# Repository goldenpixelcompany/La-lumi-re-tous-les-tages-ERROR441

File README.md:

# La lumière à tous les étages : ERROR 441
*Manuel pour allumer la lumière à tous les étages*

Voici un manuel pour apprendre à allumer la lumière à tous les étages. Et ce n’est pas toujours évident. Surtout lorsque les étages sont longs et grands et que la nature nous attribue une petite taille. Je fais un mètre soixante-neuf et j’avais besoin d’aide. Pour accomplir ma mission, je dû me faire une amie. Mais cette amie n’existait pas et nous l’avons inventée avec d’autres amis.

**Partie I : dispositif**

Nous avons choisi de réaliser cette experience à lécole des arts décoratifs de Paris. Nous étions nombreux à vouloir accomplir cette mission. Voici le batiment concerné avant et après la lumière allumée : 

Composée de 441 fenêtres d’un mètre sur un mètre vingt, la baie vitrée de l'école s’étale sur 25 mètres de haut et 21 mètres de large. Chaque fenêtre se transformerait en pixel à l'aide d'un dispositif numérique composé de Leds RGB et de papier. Tous ces dispositifs sont connectés ensembles et forment un écran dit micro-géant : Immense par ses dimensions et minuscule par sa résolution.

**Partie II : Hardware**

Pour connecter ces oixels entre eux, nous avons développer un circuit électronique adapté. Chacun d'entre eux controllait 3 pixels. Nous appelions donc les circuits les *métapixels*. Il y avait 147 circuits tous connectés en WIFI et commander par la puce ESP32. Le voici : 

**Partie III : Software**

Pour controller cet écran de pixels géant nous avons developpé le software *SEND PIX*. Essentiellement developpé par Lorris Sahli, le logiciel est à la croisée d'un outil de dessin, de gestion de pixels et d'un instrument de VJing en direct. 

Résultat des animations dessinées par le logiciel SEND PIX :

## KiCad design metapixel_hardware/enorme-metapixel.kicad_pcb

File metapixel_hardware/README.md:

# metapixel

PCB made for control the pixels on the facade. By three they come.

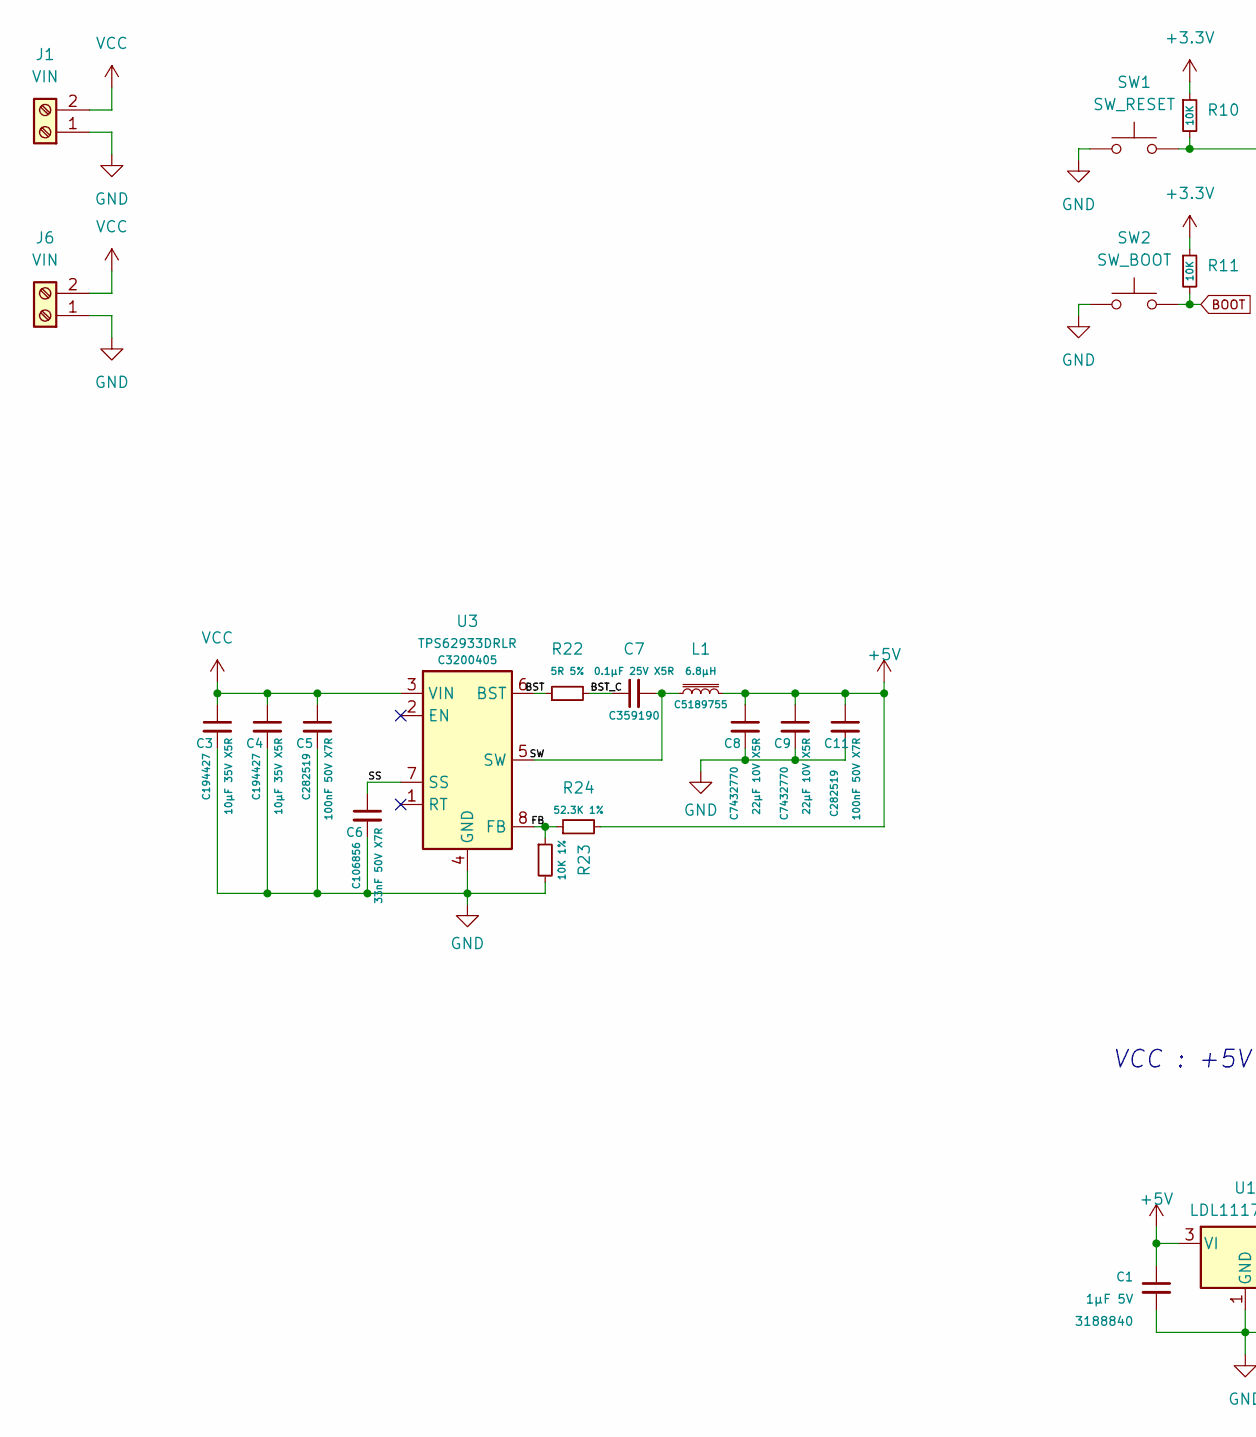
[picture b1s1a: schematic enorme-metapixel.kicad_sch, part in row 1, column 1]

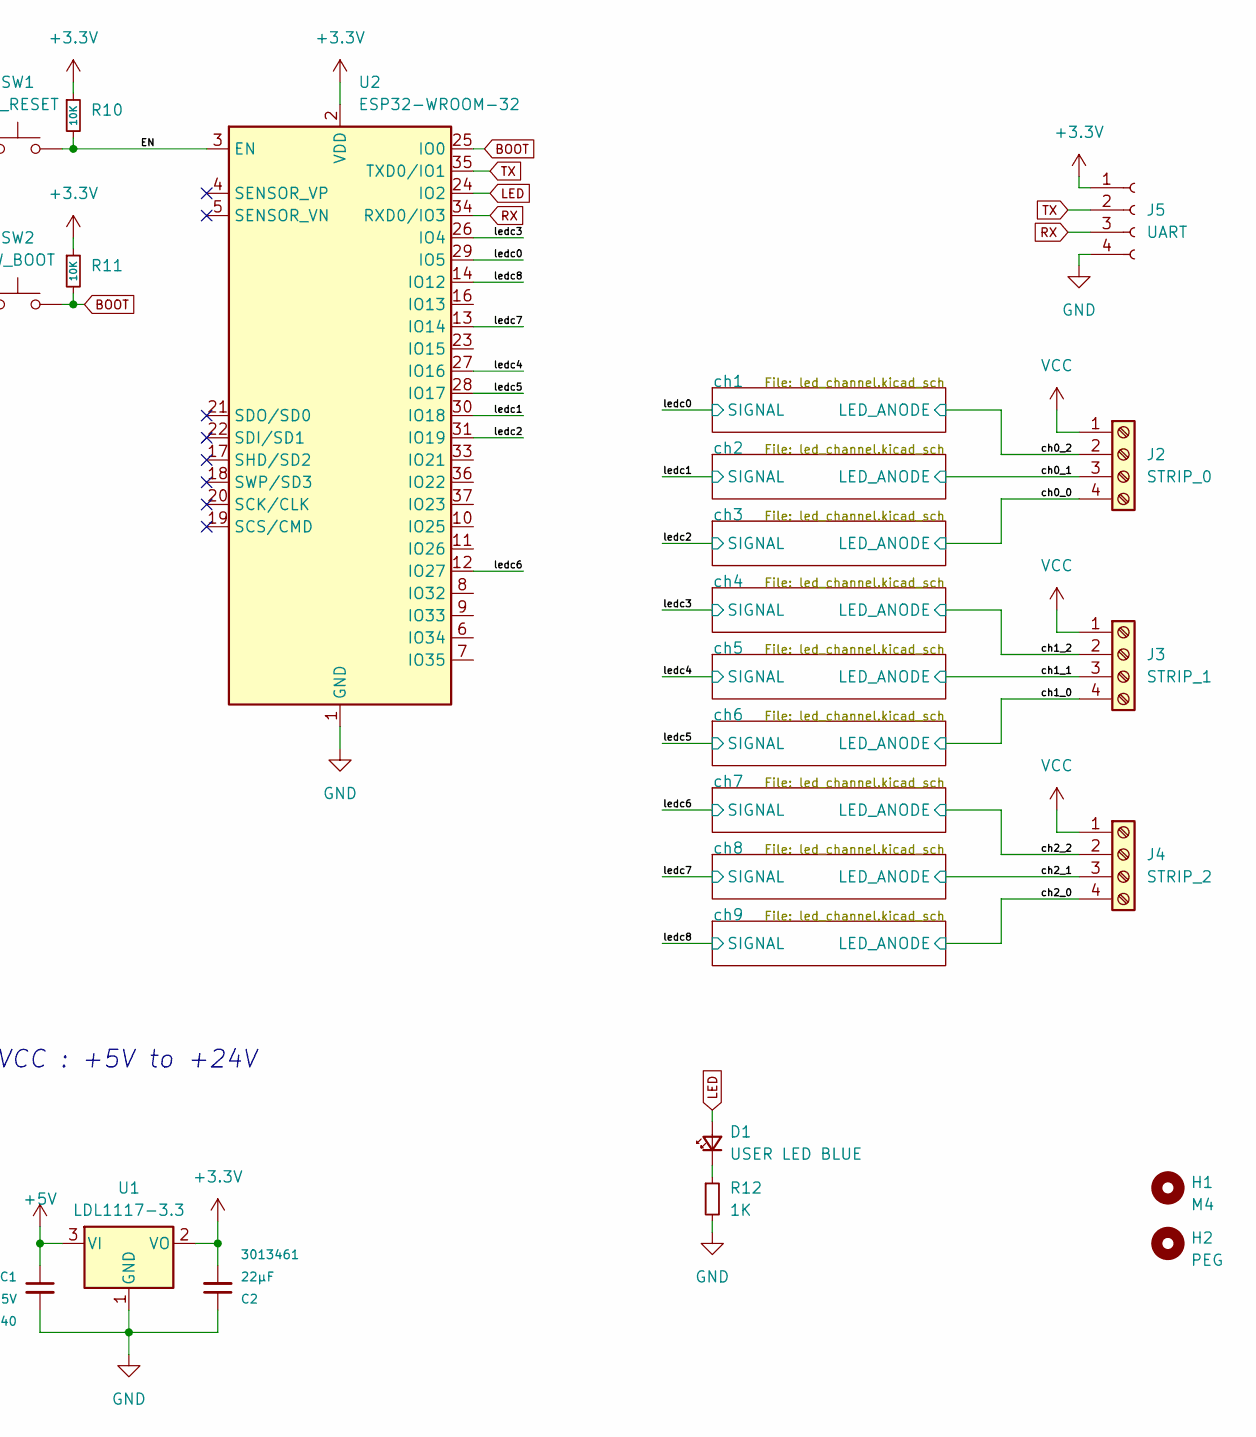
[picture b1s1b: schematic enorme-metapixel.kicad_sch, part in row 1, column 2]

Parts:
C1: 1µF 5V; C_0603_1608Metric; Farnell 3188840
C2: 22µF; C_0805_2012Metric; Farnell 3013461
C3, C4: 10µF 35V X5R; C_0603_1608Metric; LCSC C194427
C5, C11: 100nF 50V X7R; C_0603_1608Metric; LCSC C282519
C6: 33nF 50V X7R; C_0603_1608Metric; LCSC C106856
C7: 0.1µF 25V X5R; C_0402_1005Metric; LCSC C359190
C8, C9: 22µF 10V X5R; C_0603_1608Metric; LCSC C7432770
D1: USER LED BLUE; LED_0603_1608Metric; LCSC C965807
H1: M4; MountingHole_4.3mm_M4
H2: PEG; MountingHole_3.2mm_M3
J1, J6: VIN; fiche_bornier-2_P5.08mm
J2: STRIP_0; PLUG_Terminal_01x04_2.54mm
J3: STRIP_1; PLUG_Terminal_01x04_2.54mm
J4: STRIP_2; PLUG_Terminal_01x04_2.54mm
J5: UART; PinHeader_1x04_P2.54mm_Vertical
L1: 6.8µH; L_Bourns_SRP7028A_7.3x6.6mm; LCSC C5189755
R10, R11: 10K; R_0603_1608Metric
R12: 1K; R_0603_1608Metric
R22: 5R 5%; R_0603_1608Metric
R23: 10K 1%; R_0603_1608Metric
R24: 52.3K 1%; R_0603_1608Metric
SW1: SW_RESET; EVQQ2; LCSC C701204
SW2: SW_BOOT; EVQQ2; LCSC C701204
U1: LDL1117-3.3; SOT-223-3_TabPin2; LCSC C435835
U2: ESP32-WROOM-32; LCSC C82899
U3: TPS62933DRLR; SOT-583-8; LCSC C3200405

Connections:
+3.3V: C2.2, J5.1, R10.1, R11.1, U1.2 (VO), U2.2 (VDD)
+5V: C1.1, C8.1, C9.1, C11.1, L1.2, R24.2, U1.3 (VI)
/BST: R22.1, U3.6 (BST)
/BST_C: C7.1, R22.2
/EN: R10.2, SW1.2, U2.3 (EN)
/FB: R23.1, R24.1, U3.8 (FB)
/SS: C6.1, U3.7 (SS)
/SW: C7.2, L1.1, U3.5 (SW)
/ch0_0: J2.4; also elsewhere on the board
/ch0_1: J2.3; also elsewhere on the board
/ch0_2: J2.2; also elsewhere on the board
/ch1_0: J3.4; also elsewhere on the board
/ch1_1: J3.3; also elsewhere on the board
/ch1_2: J3.2; also elsewhere on the board
/ch2_0: J4.4; also elsewhere on the board
/ch2_1: J4.3; also elsewhere on the board
/ch2_2: J4.2; also elsewhere on the board
/ledc0: U2.29 (IO5); also elsewhere on the board
/ledc1: U2.30 (IO18); also elsewhere on the board
/ledc2: U2.31 (IO19); also elsewhere on the board
/ledc3: U2.26 (IO4); also elsewhere on the board
/ledc4: U2.27 (IO16); also elsewhere on the board
/ledc5: U2.28 (IO17); also elsewhere on the board
/ledc6: U2.12 (IO27); also elsewhere on the board
/ledc7: U2.13 (IO14); also elsewhere on the board
/ledc8: U2.14 (IO12); also elsewhere on the board
BOOT: R11.2, SW2.2, U2.25 (IO0)
GND: C1.2, C2.1, C3.2, C4.2, C5.2, C6.2, C8.2, C9.2, C11.2, J1.1, J5.4, J6.1, R12.2, R23.2, SW1.1, SW2.1, U1.1 (GND), U2.1 (GND), U2.15 (GND), U2.38 (GND), U2.39 (GND), U3.4 (GND); also elsewhere on the board
LED: D1.2 (A), U2.24 (IO2)
unnamed: D1.1 (K), R12.1
RX: J5.3, U2.34 (RXD0/IO3)
TX: J5.2, U2.35 (TXD0/IO1)
VCC: C3.1, C4.1, C5.1, J1.2, J2.1, J3.1, J4.1, J6.2, U3.3 (VIN)

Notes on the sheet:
VCC : +5V to +24V

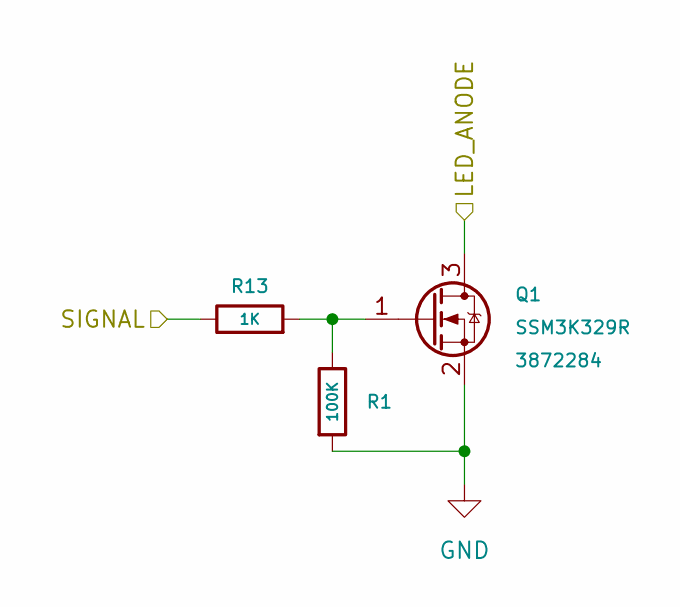
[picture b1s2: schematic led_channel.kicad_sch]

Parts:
Q1: SSM3K329R; SOT-23; Farnell 3872284
R1: 100K; R_0603_1608Metric
R13: 1K; R_0603_1608Metric

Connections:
/ch0_2: Q1.3 (D); also elsewhere on the board
/ledc0: R13.1; also elsewhere on the board
GND: Q1.2 (S), R1.2; also elsewhere on the board
unnamed: Q1.1 (G), R1.1, R13.2

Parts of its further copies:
Q2, Q3, Q4, Q5, Q6, Q7, Q8, Q9: SSM3K329R; SOT-23; Farnell 3872284
R2, R3, R4, R5, R6, R7, R8, R9: 100K; R_0603_1608Metric
R14, R15, R16, R17, R18, R19, R20, R21: 1K; R_0603_1608Metric

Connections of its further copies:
/ch0_0: Q3.3 (D); also elsewhere on the board
/ch0_1: Q2.3 (D); also elsewhere on the board
/ch1_0: Q6.3 (D); also elsewhere on the board
/ch1_1: Q5.3 (D); also elsewhere on the board
/ch1_2: Q4.3 (D); also elsewhere on the board
/ch2_0: Q9.3 (D); also elsewhere on the board
/ch2_1: Q8.3 (D); also elsewhere on the board
/ch2_2: Q7.3 (D); also elsewhere on the board
/ledc1: R14.1; also elsewhere on the board
/ledc2: R15.1; also elsewhere on the board
/ledc3: R16.1; also elsewhere on the board
/ledc4: R17.1; also elsewhere on the board
/ledc5: R18.1; also elsewhere on the board
/ledc6: R19.1; also elsewhere on the board
/ledc7: R20.1; also elsewhere on the board
/ledc8: R21.1; also elsewhere on the board
GND: Q2.2 (S), Q3.2 (S), Q4.2 (S), Q5.2 (S), Q6.2 (S), Q7.2 (S), Q8.2 (S), Q9.2 (S), R2.2, R3.2, R4.2, R5.2, R6.2, R7.2, R8.2, R9.2; also elsewhere on the board
unnamed: Q2.1 (G), R2.1, R14.2
unnamed: Q3.1 (G), R3.1, R15.2
unnamed: Q4.1 (G), R4.1, R16.2
unnamed: Q5.1 (G), R5.1, R17.2
unnamed: Q6.1 (G), R6.1, R18.2
unnamed: Q7.1 (G), R7.1, R19.2
unnamed: Q8.1 (G), R8.1, R20.2
unnamed: Q9.1 (G), R9.1, R21.2

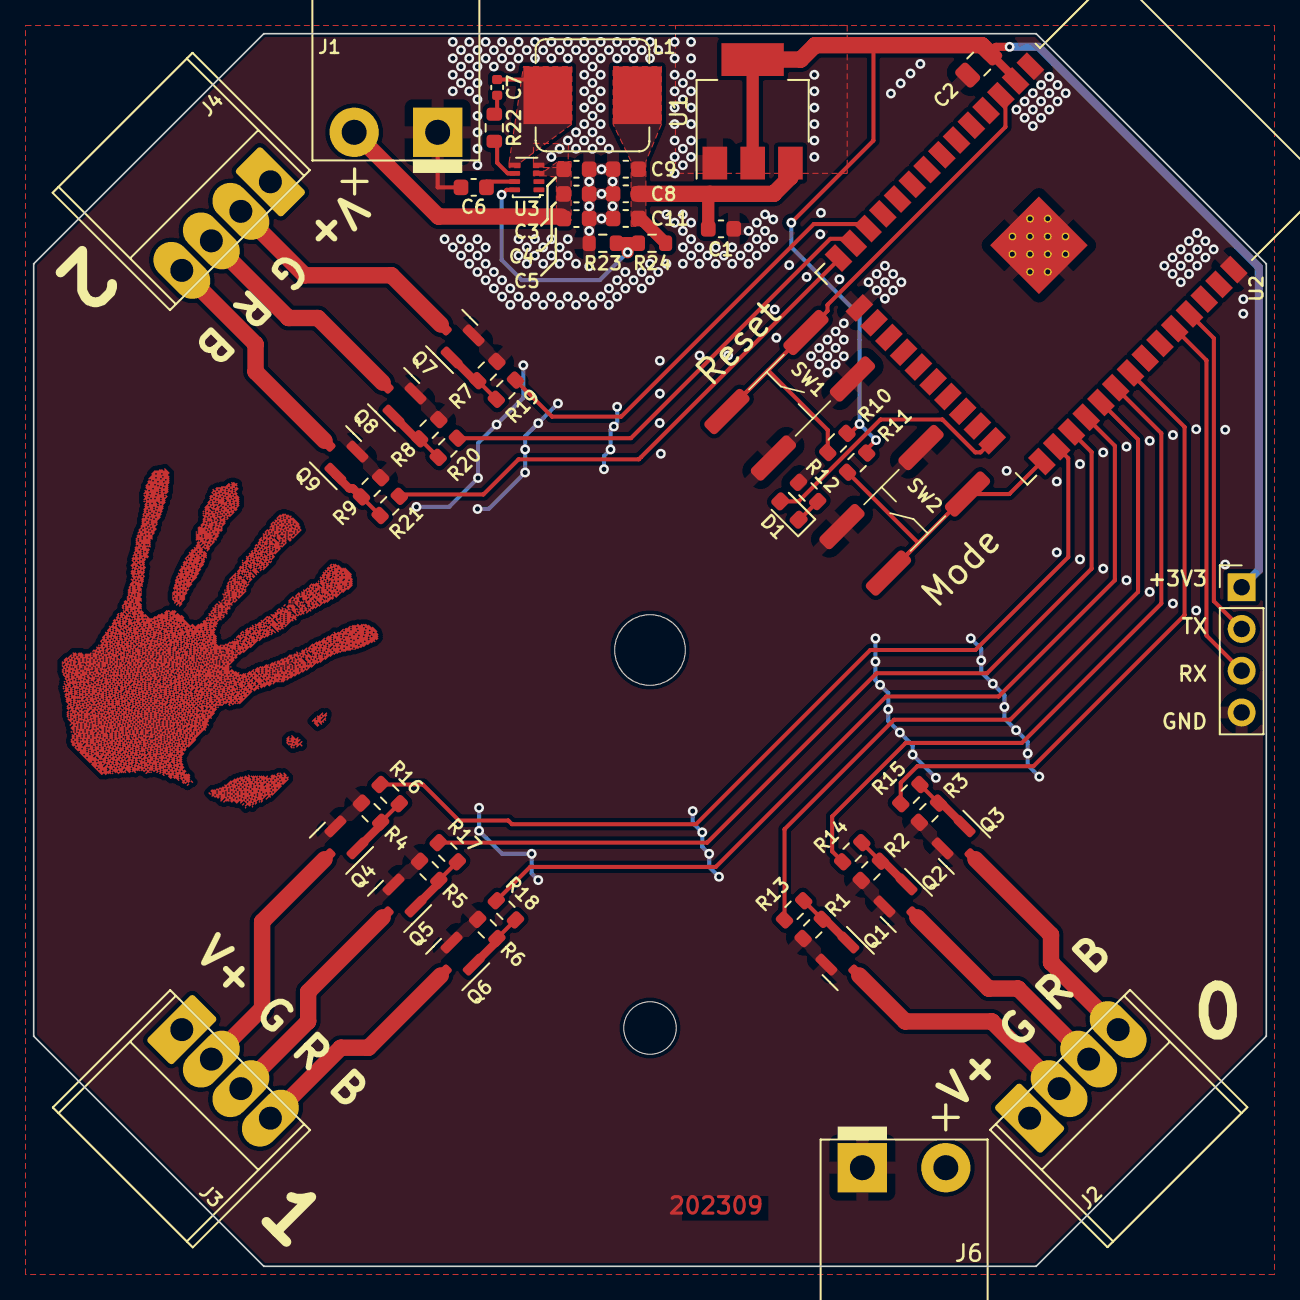
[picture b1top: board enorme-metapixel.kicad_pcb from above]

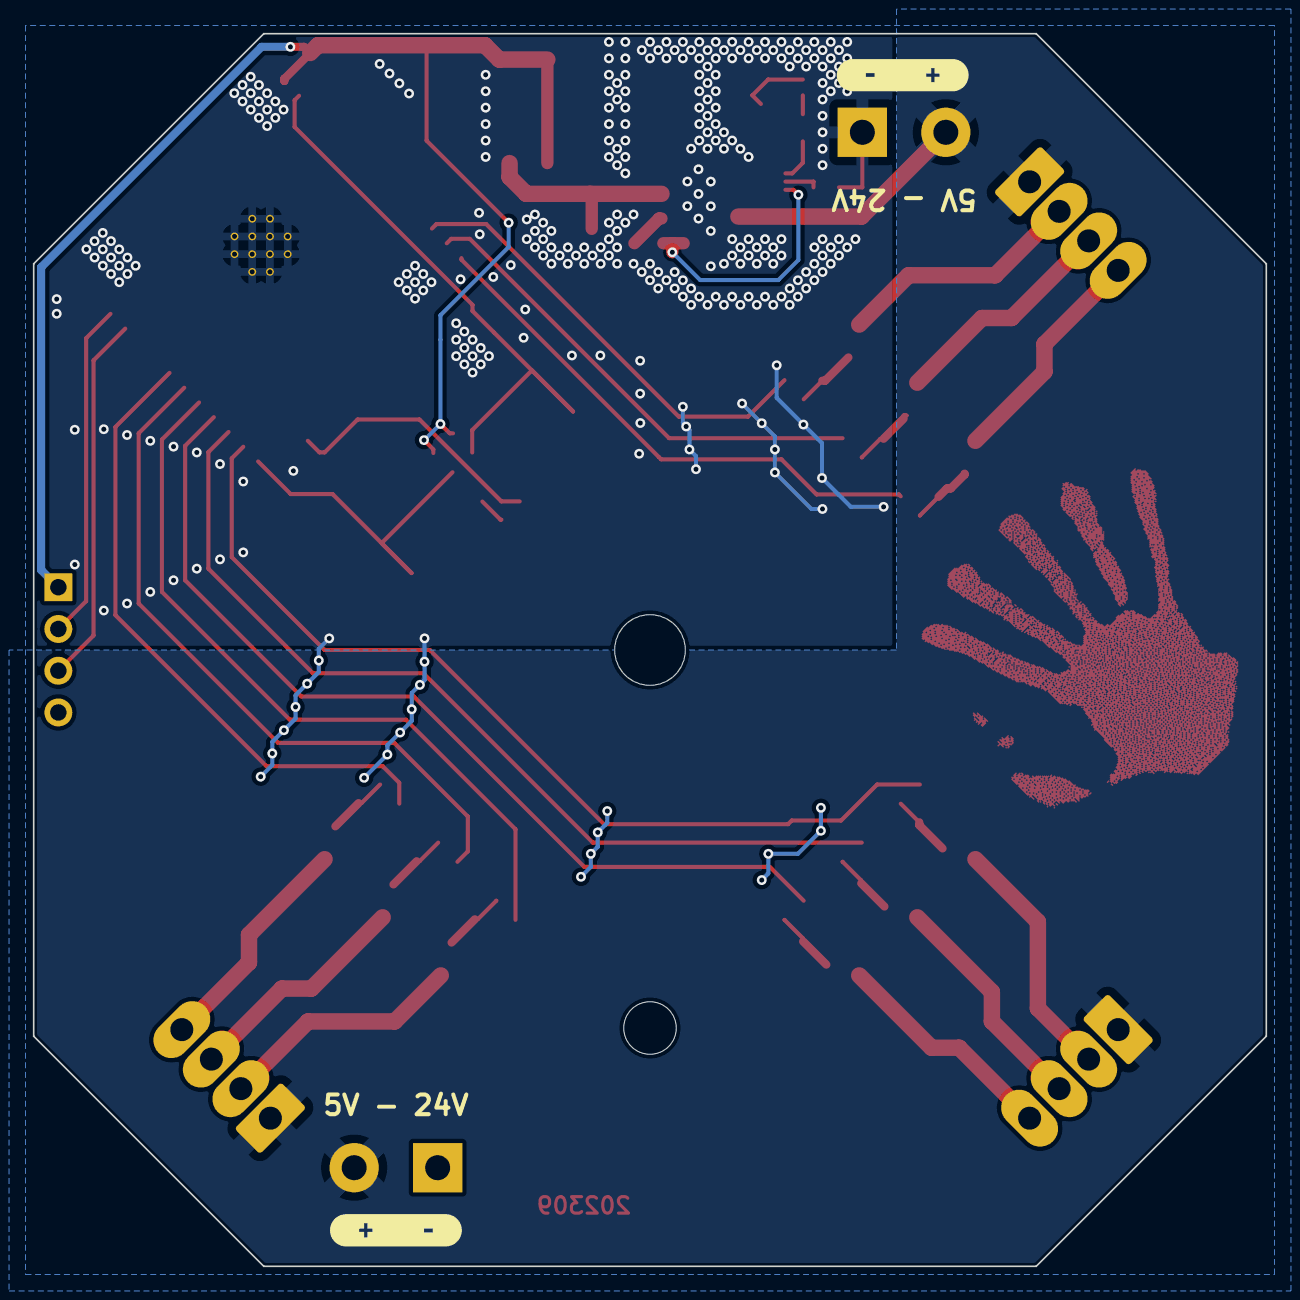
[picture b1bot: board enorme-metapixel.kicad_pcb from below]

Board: 2 copper layers, 75.0 x 75.0 mm, 60 parts (2 on the bottom side), 42 nets.

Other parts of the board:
kibuzzard-63B86E3D, kibuzzard-63B86E3D#2: G***; kibuzzard-63B86E3D

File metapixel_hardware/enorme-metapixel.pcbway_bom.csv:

,,,,,,,,
,,,T-I210W48185A 170PCS BOM  (Bill of Materials),,,,,
,,,,,,,,
,,,,,,,,
,,,,,,,,
Item #,*Designator,*Qty,Manufacturer,*Mfg Part #,Description / Value,*Package/Footprint ,Type,Your Instructions / Notes
1,C1,1,,,1µF 5V,C_0603_1608Metric,SMD,do use this exact part. LCSC # C150119
2,"C3, C4",2,Murata Electronics,GRM188R6YA106MA73D,10µF 35V X5R,C_0603_1608Metric,SMD,do use this exact part. LCSC # C150120
3,"C5, C11",2,CCTC,TCC0603X7R104K500CT,100nF 50V X7R,C_0603_1608Metric,SMD,do use this exact part. LCSC # C150121
4,C6,1,YAGEO,CC0603KRX7R9BB333,33nF 50V X7R,C_0603_1608Metric,SMD,do use this exact part. LCSC # C150122
5,C7,1,CCTC,TCC0402X5R104M250AT,0.1µF 25V X5R,C_0402_1005Metric,SMD,do use this exact part. LCSC # C150123
6,"C8, C9, C2",3,Chinocera,HGC0603R5226M100NTHJ,22µF 10V X5R,C_0603_1608Metric,SMD,do use this exact part. LCSC # C150124
7,D1,1,XINGLIGHT,XL-1608UBC-04,USER LED BLUE,LED_0603_1608Metric,SMD,do use this exact part. LCSC # C150125
8,L1,1,SHOU HAN,CYA0650-6.8UH,6.8µH,L_Bourns_SRP7028A_7.3x6.6mm,SMD,do use this exact part. LCSC # C150126
9,"Q1, Q2, Q3, Q4, Q5, Q6, Q7, Q8, Q9",9,TOSHIBA,SSM3K329R,SSM3K329R,SOT-23,SMD,do use this exact part. LCSC # C150127
10,"R1, R2, R3, R4, R5, R6, R7, R8, R9",9,,,100K,R_0603_1608Metric,SMD,
11,"R10, R11",2,,,10K,R_0603_1608Metric,SMD,
12,"R12, R13, R14, R15, R16, R17, R18, R19, R20, R21",10,,,1K,R_0603_1608Metric,SMD,
13,R22,1,,,5R 5%,R_0603_1608Metric,SMD,
14,R23,1,,,10K 1%,R_0603_1608Metric,SMD,
15,R24,1,,,52.3K 1%,R_0603_1608Metric,SMD,
16,SW1,1,PANASONIC,EVQQ2U03W,SW_RESET,EVQQ2,SMD,do use this exact part. LCSC # C701204
17,SW2,1,PANASONIC,EVQQ2U03W,SW_BOOT,EVQQ2,SMD,do use this exact part. LCSC # C701204
18,U1,1,STMicroelectronics,LDL1117S33R,LDL1117-3.3,SOT-223-3_TabPin2,SMD,do use this exact part. LCSC # C435835
19,U2,1,Espressif Systems,ESP32-WROOM-32-N4,ESP32-WROOM-32,ESP32-WROOM-32,SMD,do use this exact part. LCSC # C82899
20,U3,1,TPS62933DRLR,TPS62933DRLR,TPS62933DRLR,SOT-583-8,SMD,do use this exact part. LCSC # C3200405
21,H1,1,do not place,do not place,M4,MountingHole_4.3mm_M4,DNS / DNP,do not place / do not buy
22,H2,1,do not place,do not place,PEG,MountingHole_3.2mm_M3,DNS / DNP,do not place / do not buy
23,"J1, J6",2,do not place,do not place,VIN,bornier-2_P5.08mm,DNS / DNP,do not place / do not buy
24,J2,1,do not place,do not place,STRIP_0,PLUG_Terminal_01x04_2.54mm,DNS / DNP,do not place / do not buy
25,J3,1,do not place,do not place,STRIP_1,PLUG_Terminal_01x04_2.54mm,DNS / DNP,do not place / do not buy
26,J4,1,do not place,do not place,STRIP_2,PLUG_Terminal_01x04_2.54mm,DNS / DNP,do not place / do not buy
27,J5,1,do not place,do not place,UART,PinHeader_1x04_P2.54mm_Vertical,DNS / DNP,do not place / do not buy

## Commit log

2024-11-08 yes
    yes
2024-11-08 Code uplaoded
2024-11-08 SEND PIX Uploaded
